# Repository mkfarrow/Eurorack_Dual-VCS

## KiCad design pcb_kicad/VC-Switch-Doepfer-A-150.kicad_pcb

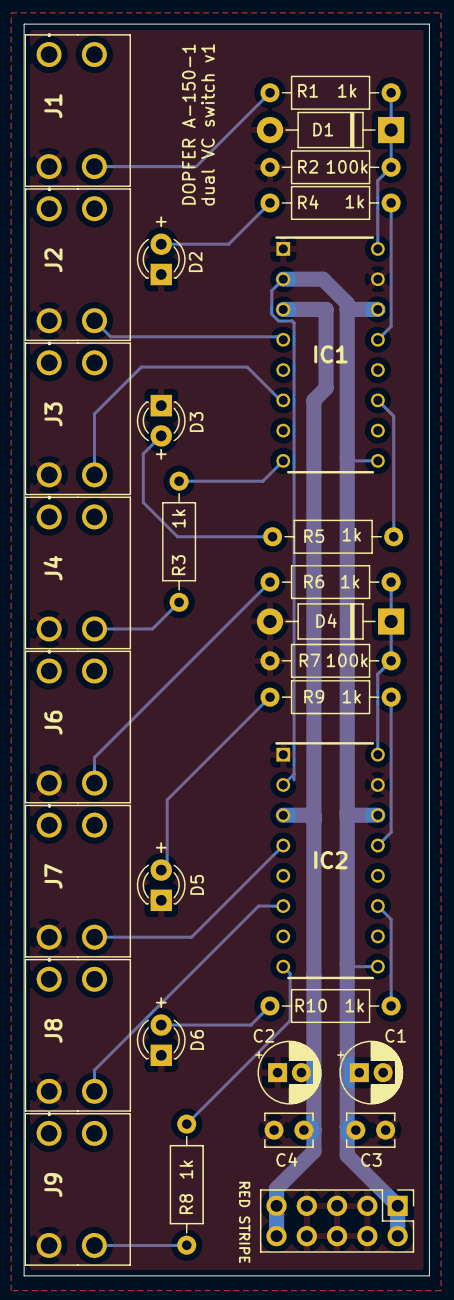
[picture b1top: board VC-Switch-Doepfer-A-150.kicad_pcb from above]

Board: 2 copper layers, 34.0 x 105.0 mm, 31 parts (0 on the bottom side), 23 nets.

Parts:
C1, C2: 10u; CP_Radial_D5.0mm_P2.00mm
C3, C4: 100n; C_Disc_D3.8mm_W2.6mm_P2.50mm
D1, D4: D; D_DO-41_SOD81_P10.16mm_Horizontal
D2, D3, D5, D6: LED; LED_D3.0mm
IC1, IC2: DG409DJ; DIP794W56P254L1917H533Q16N
J1, J6: CV in; CL1384
J2, J7: I/O1; CL1384
J3, J8: I/O2; CL1384
J4, J9: O/I; CL1384
J5: EURO_PWR_2x5; PinHeader_2x05_P2.54mm_Vertical
R1, R3, R4, R5, R6, R8, R9, R10: 1k; R_Axial_DIN0207_L6.3mm_D2.5mm_P10.16mm_Horizontal
R2, R7: 100k; R_Axial_DIN0207_L6.3mm_D2.5mm_P10.16mm_Horizontal

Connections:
+12V: C1.1, C3.1, IC1.2, IC1.9, IC1.14, IC2.2, IC2.9, IC2.14, J5.1, J5.2
-12V: C2.2, C4.2, IC1.3, IC2.3, J5.9, J5.10
GND: C1.2, C2.1, C3.2, C4.1, D1.2, D2.1, D3.1, D4.2, D5.1, D6.1, IC1.1, IC1.15, IC2.1, IC2.15, J1.S, J2.S, J3.S, J4.S, J5.3, J5.4, J5.5, J5.6, J5.7, J5.8, J6.S, J7.S, J8.S, J9.S, R2.2, R7.2
unnamed: D1.1, IC1.16, R1.1, R2.1
unnamed: D2.2, R4.2
unnamed: D3.2, R5.2
unnamed: D4.1, IC2.16, R6.1, R7.1
unnamed: D5.2, R9.2
unnamed: D6.2, R10.2
unnamed: IC1.4, J2.T
unnamed: IC1.6, J3.T
unnamed: IC1.8, R3.2
unnamed: IC1.11, R5.1
unnamed: IC1.13, R4.1
unnamed: IC2.4, J7.T
unnamed: IC2.6, J8.T
unnamed: IC2.8, R8.2
unnamed: IC2.11, R10.1
unnamed: IC2.13, R9.1
unnamed: J1.T, R1.2
unnamed: J4.T, R3.1
unnamed: J6.T, R6.2
unnamed: J9.T, R8.1

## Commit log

2022-06-10 adding files for panel
2022-12-22 adding images
2023-02-24 added kicad project for PCB
